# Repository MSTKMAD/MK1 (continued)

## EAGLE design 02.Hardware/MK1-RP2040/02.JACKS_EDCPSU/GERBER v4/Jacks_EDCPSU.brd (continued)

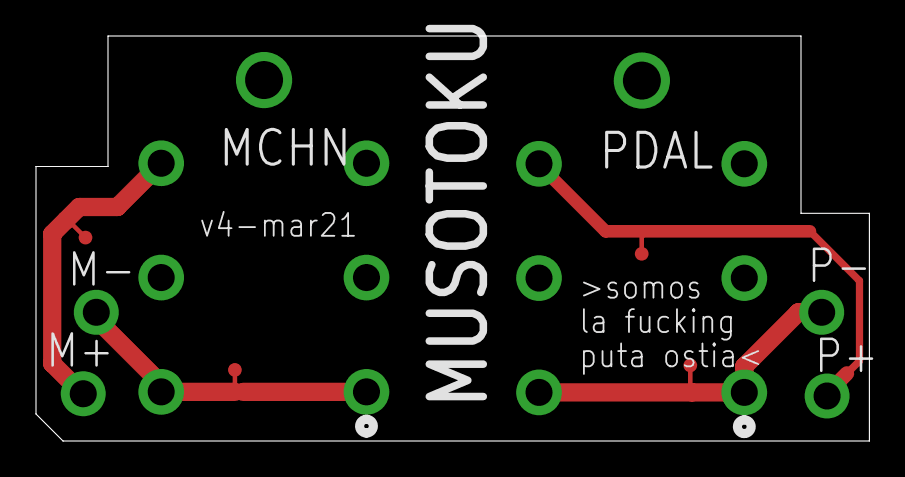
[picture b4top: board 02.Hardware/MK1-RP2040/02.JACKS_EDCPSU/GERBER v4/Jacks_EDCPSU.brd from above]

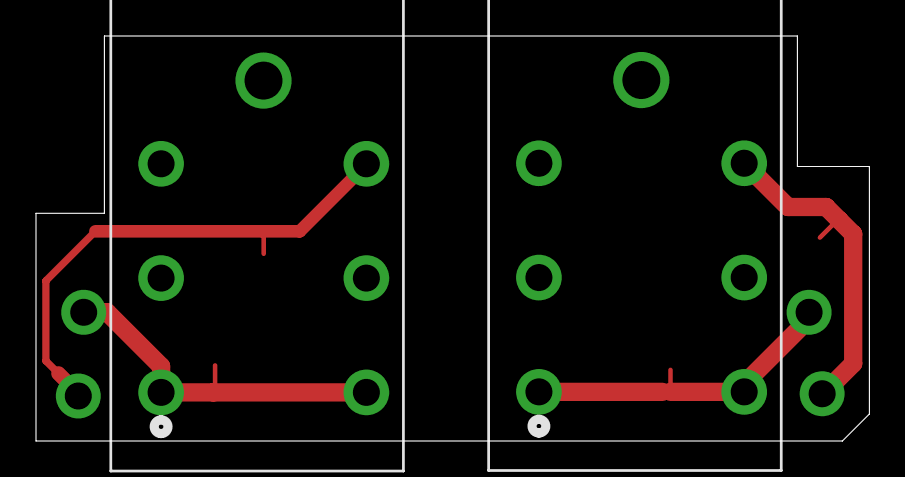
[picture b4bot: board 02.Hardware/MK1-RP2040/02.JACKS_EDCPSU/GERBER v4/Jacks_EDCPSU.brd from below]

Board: 2 copper layers, 46.3 x 22.5 mm, 6 parts (2 on the bottom side), 4 nets.

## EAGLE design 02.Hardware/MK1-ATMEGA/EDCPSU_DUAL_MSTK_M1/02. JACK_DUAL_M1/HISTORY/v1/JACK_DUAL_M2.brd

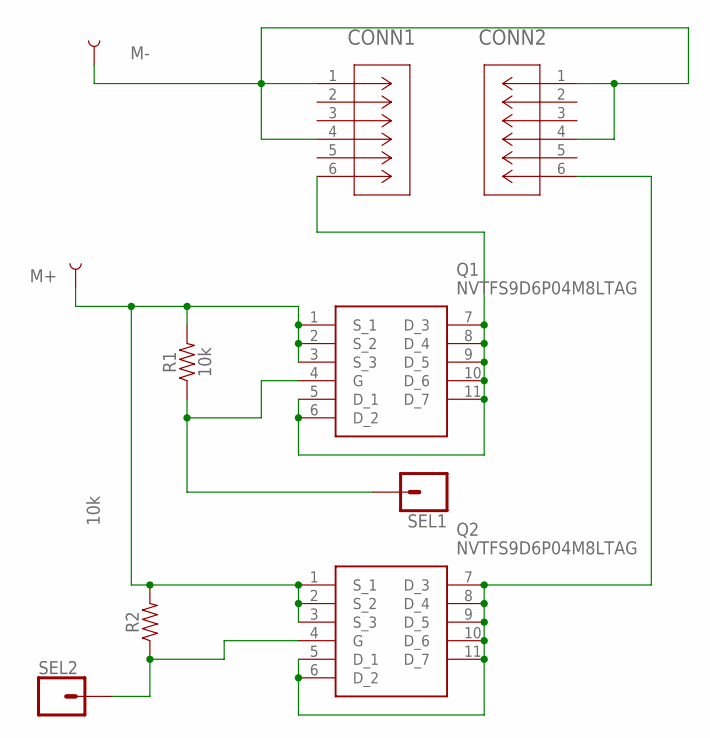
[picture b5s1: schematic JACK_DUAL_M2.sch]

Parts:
CONN1, CONN2: ACJS-MHDR; CONN_MHDR_AMP
M+: TEST-POINT3; PAD.03X.03
M-: TEST-POINT3; PAD.03X.03
Q1, Q2: NVTFS9D6P04M8LTAG; NVTFS5124PLTWG
R1, R2: 10k; 0805
SEL1, SEL2: CONN_01; 1X01

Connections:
GND: CONN1.1, CONN1.4, CONN2.1, CONN2.4, M-.P$1
M+: M+.P$1, Q1.1 (S_1), Q1.2 (S_2), Q1.3 (S_3), Q2.1 (S_1), Q2.2 (S_2), Q2.3 (S_3), R1.2, R2.2
unnamed: CONN1.6, Q1.5 (D_1), Q1.6 (D_2), Q1.7 (D_3), Q1.8 (D_4), Q1.9 (D_5), Q1.10 (D_6), Q1.11 (D_7)
unnamed: CONN2.6, Q2.5 (D_1), Q2.6 (D_2), Q2.7 (D_3), Q2.8 (D_4), Q2.9 (D_5), Q2.10 (D_6), Q2.11 (D_7)
unnamed: Q1.4 (G), R1.1, SEL1.1
unnamed: Q2.4 (G), R2.1, SEL2.1

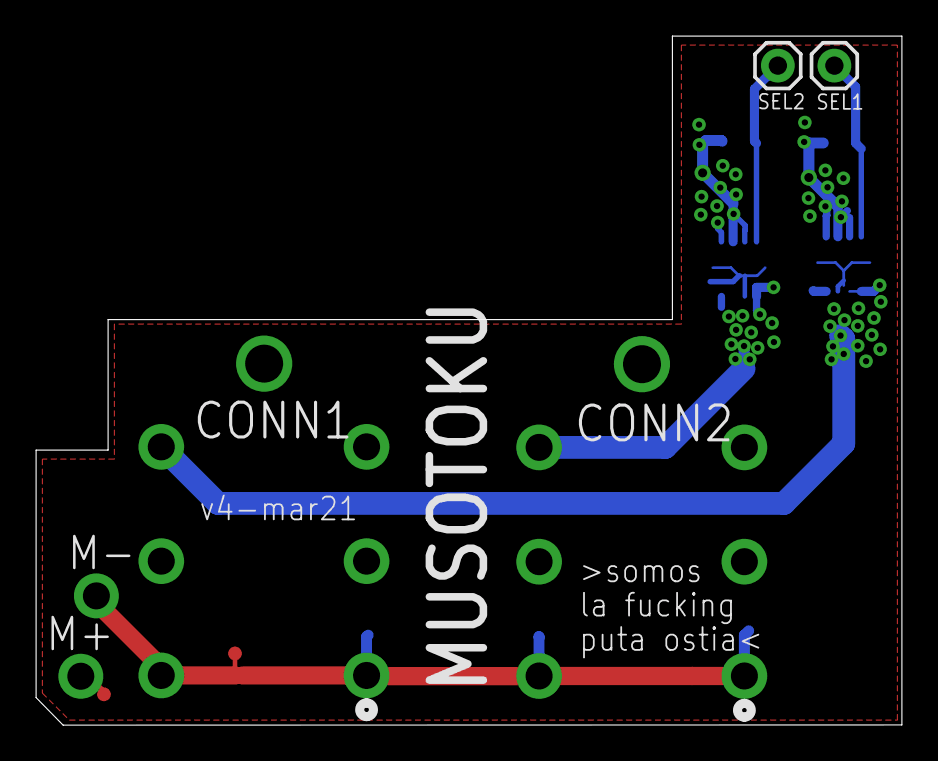
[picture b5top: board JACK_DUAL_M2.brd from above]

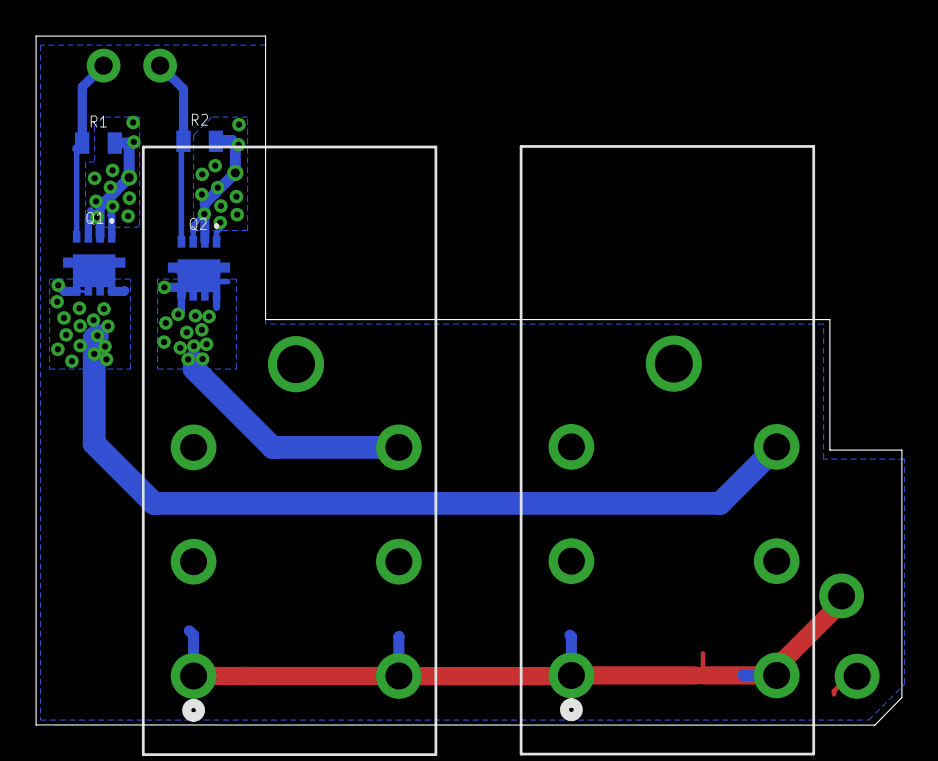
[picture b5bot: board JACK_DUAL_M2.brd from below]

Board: 4 copper layers, 48.1 x 38.3 mm, 10 parts (6 on the bottom side), 6 nets.

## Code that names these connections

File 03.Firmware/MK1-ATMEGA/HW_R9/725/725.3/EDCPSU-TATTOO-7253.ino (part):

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const int OVC_UVOLT_MAX_TIME = 1000;          // Maximum time that can last the overcurrent with the UNDERVOLTAGE method (Milliseconds)
const unsigned int OVC_SENSE_LIMIT_INF = 760; // Current limit above which it is still considered an overcurrent sense situation 2.6A
const unsigned int OVC_SENSE_LIMIT_SUP = 800; // Current limit above which it is Triggered the overcurrent sense situation 2.7A real (in theory this value should trigger at 3.1A but Rsense is contaminated by a trace track to the amplifier)
const byte MAX_OVC_ERRORS = 5;                // Max number of OVC errors per session in order to request the release of the PEDAL to the user
const int UNDERVOLT_1V5 = 100;                // Sensed voltage corresponding to 2V for undervoltage sensing
const int UNDERVOLT_1V8 = 121;                // Sensed voltage corresponding to 1.8V for undervoltage sensing
const float DISP_TO_VTARGET_CONV = 5.2;       // Conversion factor to get display values into same scale as VoutSense values (1/19.6)*1023 = 52.2 --> to DISP 52/10=5.2
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const unsigned long RX_CHAR_TIMEOUT = 10; // (ms) time allowed for an orphan char received via Serial
const byte TLG_RX_BYTES = 3;              // Bytes compounding a Serial telegram of the Test mode

const byte ALARM_FLAG = 0; // Flag to report that OVC_ALARM sensor is activated. This is set in ReportFlags report byte in the Test Mode
const byte PEDAL_FLAG = 1; // Flag to report that PEDAL input is activated. This is set in ReportFlags report byte in the Test Mode
// ------------------------------------------------- PIN DEFINITION r7,r6 -------------------------------------------
const int DCDC_EN = A1;  //
const int LED_FRONT = 9; // Arduino 7 (pin 11 in ATMEGA368)
const int CHG_POL = 7;   // Arduino 9 (pin 13 in ATMEGA368)
const int ISEN = A7;
const int VOSEN = A6;
const int PUSHBUTTON_IP = A2; // HIGH = OFF; LOW = ON
const int ROTPUSH_IP = A3;    // HIGH = OFF; LOW = ON
const int ROTA = 4;
const int OVC_ALARM = 5; // New in r8.0 (before pin 2)
const int ROTB = 3;
const int BUZZ = 6;
const int PEDAL_IP = 2;      // New in r8.0 (before pin 5)
const int ANALOG_PEDAL = A0; // New in r8.0 (before LED)

//-------------------------- PROGMEM DEFINITION -----------------------------------------------------------------
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    134, 135, 136, 137, 138, 139, 140, 141, 142, 143, 144, 145, 146, 147, 148, 149, 150, 151, 152, 153, 154, 155, 156, 157,
    158, 159, 160};

PROGMEM const byte NitroLookupTableLow[LenNITROLookupTable] = {1, 3, 11, 21, 36, 51, 63, 71, 74, 75, 76, 76, 76, 75, 74, 73, 73, 72, 71, 71};  // Vout= 2-(nitro_encoder*0.1) These are encoderPos location along the TPICLookupTable (max volt=9.3)
PROGMEM const byte NitroLookupTableHigh[LenNITROLookupTable] = {1, 2, 11, 21, 36, 51, 68, 80, 93, 96, 98, 99, 99, 99, 96, 94, 90, 90, 90, 90}; // Vout= 2-(nitro_encoder*0.1) These are encoderPos location along the TPICLookupTable (max volt=9.3)

// ------------------------------------------ FUNCTIONS --------------------------------------
void Write_TPIC2810(byte address, byte data);
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int NitroForContinuousMode;               // This varible enables the "RISE event" of the continuous mode and therefore facilitates the Nitro
unsigned long PartialRuntimer = 0;        // Runtimer counter that accounts for the current segment of time being added up to the total counter.
                                          // Each time that it is around 1 minute accumulated, it is transferred to the TotalRuntimer and the PartialRuntimer is cleared.
unsigned long TotalRuntimer = 0;          // Accounts for the total run time of this session
byte RuntimerEnable = true;               // Variable used for getting noticed for Runtimer to run.
int runningHours;                         // Used by Runtimer
int runningMinutes;                       // Used by Runtimer
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unsigned long ShowLongPressTimer;           // Timer to control the longpress information shown on display (Milliseconds)
byte ShowLongpressInfo = NO_LONGPRESS_INFO; // ATTENTION: Global var! Determines if Longpress info has to be shown. Used on other display
                                            // functions to enable or not the display info.
byte OVCerrorsConsecutive = 0;              // Number of consecutive OVC errors. After reached a limit, it is requiered that pedal is released by user in order to continue

byte RxBuffer;                  // Number of bytes received at Serial
unsigned long TimedataInBuffer; // Timer for Serial reception in Test Mode
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  pinMode(ANALOG_PEDAL, INPUT);
  pinMode(PUSHBUTTON_IP, INPUT);
  pinMode(ROTPUSH_IP, INPUT);
  pinMode(ROTA, INPUT);
  pinMode(ROTB, INPUT);
  pinMode(BUZZ, OUTPUT);
  pinMode(PEDAL_IP, INPUT);
  pinMode(ISEN, INPUT);
  pinMode(VOSEN, INPUT);
  pinMode(DCDC_EN, OUTPUT);
  pinMode(CHG_POL, OUTPUT);
  pinMode(OVC_ALARM, INPUT);

  //-----------------

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      }
    }

    //--Performs Spin Action depending on Run Mode--
    if (RotaryDebounced == true)
    {
      EncoderChangePrev = EncoderChange; // EncoderChangePrev is ONLY updated once the spin direction change is consolidated
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
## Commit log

2023-06-05 Initial Commit.
    Subido y volcado de todos los archivos relacionados con el repositorio de la machete MK1, sin introducir ningún cambio.
2023-06-06 Migracion inicial de Atmega a RP2040. Basada en version 805 de la MK2.
2023-06-06 Formateo de espacio y saltos de linea
2023-08-10 Archivos necesarios para la compilacion.
    Compile.bat
    Upload2RP
    Librerias
2023-08-10 Versión 740 release candidate
2023-08-10 Update Gitignore
    .Ds-store file ignored
2023-10-04 Creacion de Version RP2040
2023-10-04 Conectores v4 compatibles con version rp2040
2023-10-05 Creación de BOM v1 MK1-RP2040
2023-11-16 Update Gitignore
    Exclusion de los archivos redundantes de Eagle.
    Exclusion Carpeta /buils
2023-11-16 Actualizacion BOM MK1 RP2040
2023-11-16 Actualizacion BOM MK1 RP2040 y cambios menores
    Se agranda los agujeros laterales del rotary.
    Intercambio de posición de las vías del pedal.
    Acortamiento de la peninsula.
2023-11-16 actualizacion csv BOM MK1 RP2040
2023-12-13 Cambio del Mensaje inicial
2023-12-13 Ajuste del tiempo de pulsacion larga
2023-12-13 Cambio del logo inicial
2023-12-13 Ajustes de la proteccion UnderVoltaje
2023-12-13 Nuevo Nitro Ajustado
    Se alarga la escalera de subida del nitro de 50ms a 200ms
2023-12-13 Actualización de Archivo de programacion
2023-12-13 Actualizacion de librerias
2023-12-13 Ajuste del limite de corriente.
    Debido al aumento de la resistencia por el trazo en la PCB en la resistencia de sensado, es necesario reajustar el limite de corriente.
2023-12-14 Formating
2023-12-14 Nueva deteccion de cortocircuito
2023-12-14 Formating RP2040
2023-12-14 Nuevo Nitro para RP2040
    50ms a 5v.
    Escalera de 200 ms a 12v.
    Escalera de descenso de 60ms a Voltaje deseado.
2023-12-14 Update Gitignore
2024-01-18 gitnore update
2024-01-22 Cierra issue #2 y revision general para peticion de fabricacion SETI
    Revision general.
    Se añade detalles menores.
    Cierra issue #2
2024-01-22 Ficheros de fabricacion para SETI. Produccion Enero 2024 (1ra)
    Produccion Enero 2024 (1ra)
2024-04-02 Fix error
    Debido a un error de indexacion. La proteccion se Undervoltage se habia quedado supeditada y no iba a cotejarse nunca.
2024-04-02 Revert "Fix error"
    This reverts commit 3b57b25a1eaec21b558d9d443407cf5f91aafbc8.
2024-04-02 Fix error
2024-04-09 Cierra el issue #4
    Cambio en el temporizador de la proteccion de cortocircuito
2024-04-09 Actualizacion de Version
    Version 750: Proviene de la version 805 de la MK2 debido al cambio de microcontrolador con respecto a la version 740.
2024-04-17 Test MKxRp2040
    v1
2024-10-21 Actualizacion con el ADC externo de 4 canales
2024-10-30 Actualizacion Test Plug v2. Solo Resistencia de 6Ohm
2025-02-11 Troubleshotting display
2025-02-11 PCB Test plug v1
2025-02-11 Test MKx modificacion valores
2025-02-11 MK1 RP2040
2025-02-11 MK1 ATMEGA
2025-02-11 Driver ADC
2025-02-11 PCB MK1 RP2040- Pines RX TX
2025-04-22 New USBC MK1
2025-07-03 Version 1 para Seti Mk1 USBC Rp2040
2025-10-06 Version USB-C
2025-10-07 FIXBUG: Display
    Se cambia la libreria del ssd1306 a la de la MK2 para solucionar el bug de que no se encienda la pantalla.
2025-10-07 FIXBUG: Borrado EEPROM
    Se mueve la inicializacion despues de los 2 segundos del icono para prevenir que debido a malc ontacto del conector de entrada, la lectura de la eeprom se pueda corromper
2026-01-16 gitignore
2026-01-16 Finish
